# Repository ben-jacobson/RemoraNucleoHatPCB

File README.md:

# Remora Nucleo-144 Hat PCB.
Work in progress design for a cost-effective, highly customisable LinuxCNC motion control unit.

Form factor is a hat/shield for ST Nucleo-144 evaluation board running [Remora](https://github.com/scottalford75/Remora). Requires a WIZNet TOE for Ethernet control. A link to a specific recommended version of Remora can be found below but other versions should work. This unit is capable of controlling a variety of machine types including CNC milling machines, routers, lathes, laser and plasma cutters. 

Schematics and board layout are editable with Kicad 9. Gerbers and PDF's of the schematics will become available on release. At this stage the design is pre-release with a lot of validation/testing/design work pending. 

## Proposed Features
- **Low cost**: Board can be fabricated via PCBWay, parts can be ordered from Digikey/Mouser/Element14. Digikey part numbers are written into the BOM for easy ordering. My latest build was sponsored by PCBWay but their estimated cost was just under the $100USD mark not including shipping 
- **Approachable**: Goal is to be well documented, providing step by step build guides.
- **Moderate skill requirement**: SMT soldering skills are required but the pad sizes are forgiving enough for hand soldering. Hot air or reflow oven soldering is possible but not required. 

## Current spec
- Nucleo-144 Hat for 6 axis LinuxCNC motion control using custom port of Remora built for STM32. Board may also support GrblHAL but is not yet tested. 
- Up to 6 axes of isolated, step generation. Default max step gen rate in Remora is 40Khz but the driver circuitry has been tested to generate clean step pulses up to 100Khz. Can be used with any 5V single ended or differential stepper driver. Unused axes can be reconfigured as differential digital outputs. 
- IO: 16x digital inputs, 8x NPN digital outputs. Outputs are sink logic/open collector, protected by a fuse and can sink up to 40mA of current. 
- Most outputs can be configured to drive PWM signals, see the readme in the firmware below for available pins and how to configure this.
- IO: 2x analog inputs (non isolated)
- 1x 0-5v / 0-10v DAC for spindle control. Additional spindle control such as direction or indexing can be achieved with IO.
- 24V DC power input for powering the Nucleo which in turn supplies 5V and 3.3V to sections of the board that are isolated. Galvanic isolation between Nucleo and external devices is achieved by supplying your own isolated 24V supply to the separate input. A jumper can be configured on board to powering the board with only one supply, but will break the isolation.  
- Console logging is available via a UART header (TX only, RX is not used by firmware).

## Future Specs
- PSU's seem to be fine handling 18-28V, need to test this before officially marking this as in spec. 
- There is an experimental single ended ABZ Rotary Encoder Input, it was hobbled together from parts already available on the BOM as an experiment. Predictably it does not perform any high speed task, it would probably even struggle with a slowly moved rotary encoder pot. Will eventually replace with a real design. 

## Build guide
This is intended to be a DIY project, not as a complete product.
A link will soon be provided to a place to order on PCBWay, or you can self source the parts using the DigiKey part numbers.
Please see the jumper settings and connecting to USB section as they are contain important information needed to get started.

**Jumper settings:**
Before powering on your Nucleo hat, ensure that the following two jumpers are set: 
JP1: Please remove this jumper entirely
JP3: Place to the far right position, indicating VIN as per the picture in JP3Setting.png

**Connecting to USB:**
Take care when connecting the device to USB. Please make sure that the board is fully powered up before connecting to USB. Failing to do so could result in damage to your computer. This is not an issue with our design, but in the Nucleo itself. For more info see 7.4.2 in the Nucleo 144 datasheet. The device does not need USB to run. USB can be used to flash new firmware or monitor serial output. For serial output, the provided TX pin header is a better choice if you'd like constant serial monitoring during use.

## Todos
- Perform full board testing with a real load and measure current draws, re-design the PSU's for beter efficiency, line/load regulation, ripple rejection, etc. 
- Add PTC resettable fuses to PSU
- Commit release Gerber files to repo and PDF
- Put up some photos of the completed PCB.
- Put up marketplace product on PCBWay
- Research how we might be able to support Servo drives
- Test GRBLHal

## If you'd like to contribute into this project
Reach out - would love some help with any improvement. Would be especially grateful for anyone willing to help with testing, further engineering support, etc.

## Firmware
Firmware can be found in separate repo: https://github.com/ben-jacobson/Remora-STM32F4xx-PIO

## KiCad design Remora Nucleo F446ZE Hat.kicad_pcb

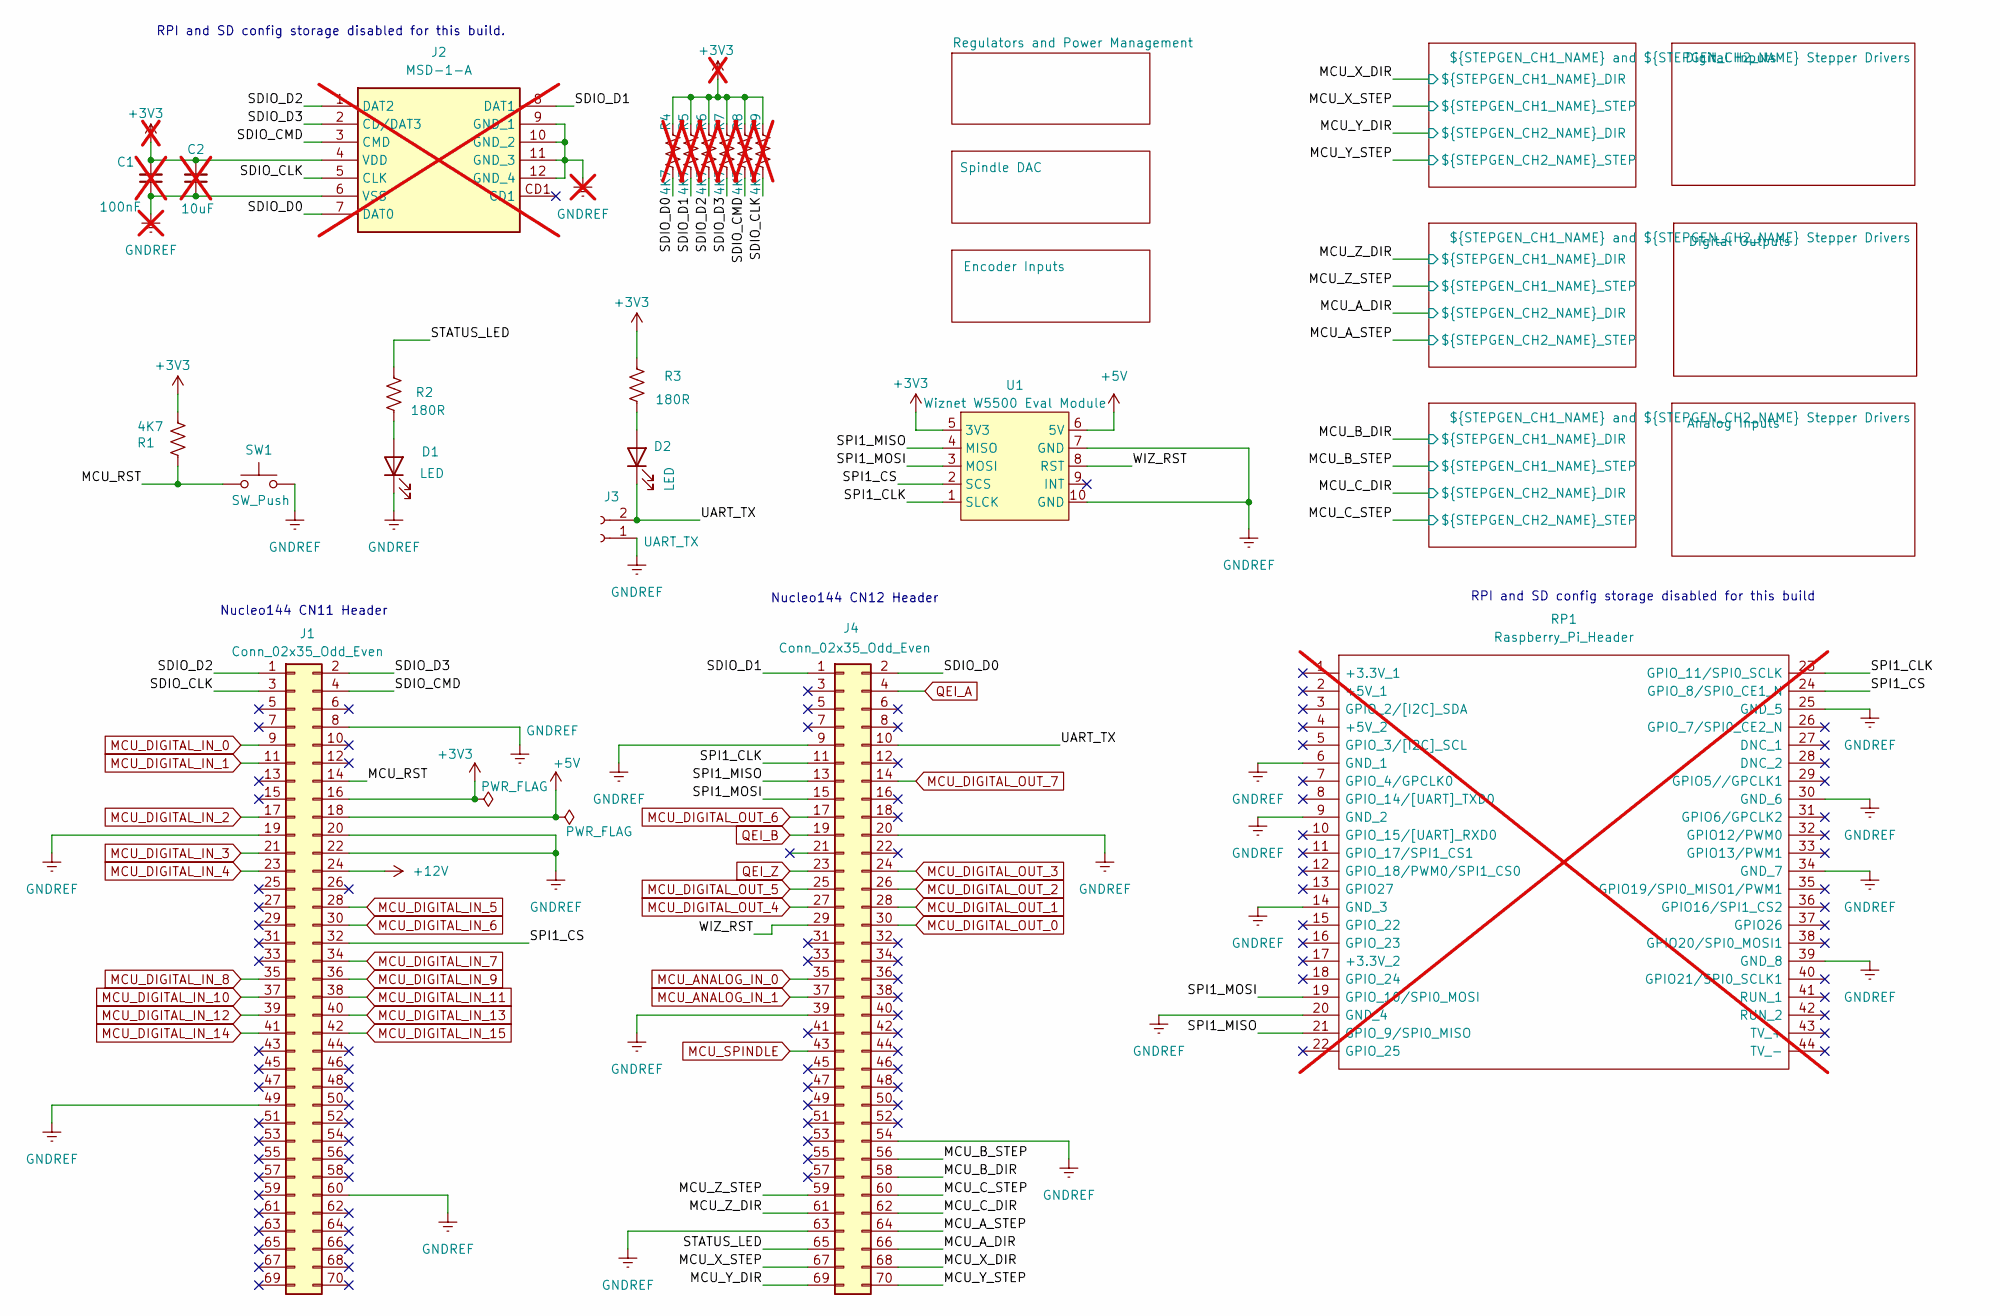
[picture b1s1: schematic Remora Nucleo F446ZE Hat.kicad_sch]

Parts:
C1: 100nF; C_1206_3216Metric_Pad1.33x1.80mm_HandSolder; Digikey Part Number 399-C1206C104K5RACTUCT-ND; not fitted
C2: 10uF; C_1206_3216Metric_Pad1.33x1.80mm_HandSolder; Digikey Part Number 1276-1804-1-ND; not fitted
D1, D2: LED; D_1206_3216Metric_Pad1.42x1.75mm_HandSolder; Digikey Part Number 3147-B1501USD-20D000313U1930CT-ND
J1, J4: Conn_02x35_Odd_Even; PinHeader_2x35_P2.54mm_Vertical; Digikey Part Number SSW-135-03-T-D-ND
J2: MSD-1-A; MSD1A; Manufacturer_Part_Number MSD-1-A; Mouser Part Number 179-MSD-1-A; not fitted
J3: UART_TX; PinHeader_1x02_P2.54mm_Vertical; Digikey Part Number PH1-02-UA
R1: 4K7; R_1206_3216Metric_Pad1.30x1.75mm_HandSolder; Digikey Part Number 311-4.70KFRCT-ND
R2, R3: 180R; R_1206_3216Metric_Pad1.30x1.75mm_HandSolder; Digikey Part Number 311-180FRCT-ND
R4, R5, R6, R7, R8, R9: 4K7; R_1206_3216Metric_Pad1.30x1.75mm_HandSolder; Digikey Part Number 311-4.70KFRCT-ND; not fitted
RP1: Raspberry_Pi_Header; raspberrypi_2_3; Manufacturer_Part_Number Raspberry Pi 2 or 3; Digikey Part Number SAM1204-20-ND; not fitted
SW1: SW_Push; SW_SPST_Omron_B3FS-100xP; Digikey Part Number SW424CT-ND
U1: Wiznet W5500 Eval Module; W5500EvalModule; Digikey Part Number SAM12520-ND

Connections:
+3V3: C1.2, C2.2, J1.16, J2.4 (VDD), R1.1, R3.1, R4.1, R5.1, R6.1, R7.1, R8.1, R9.1, U1.5 (3V3); also elsewhere on the board
+5V: J1.18, U1.6 (5V)
+12V: J1.24; also elsewhere on the board
/MCU_A_DIR: J4.66; also elsewhere on the board
/MCU_A_STEP: J4.64; also elsewhere on the board
/MCU_B_DIR: J4.58; also elsewhere on the board
/MCU_B_STEP: J4.56; also elsewhere on the board
/MCU_C_DIR: J4.62; also elsewhere on the board
/MCU_C_STEP: J4.60; also elsewhere on the board
/MCU_RST: J1.14, R1.2, SW1.1
/MCU_X_DIR: J4.68; also elsewhere on the board
/MCU_X_STEP: J4.67; also elsewhere on the board
/MCU_Y_DIR: J4.69; also elsewhere on the board
/MCU_Y_STEP: J4.70; also elsewhere on the board
/MCU_Z_DIR: J4.61; also elsewhere on the board
/MCU_Z_STEP: J4.59; also elsewhere on the board
/SDIO_CLK: J1.3, J2.5 (CLK), R9.2
/SDIO_CMD: J1.4, J2.3 (CMD), R8.2
/SDIO_D0: J2.7 (DAT0), J4.2, R4.2
/SDIO_D1: J2.8 (DAT1), J4.1, R5.2
/SDIO_D2: J1.1, J2.1 (DAT2), R6.2
/SDIO_D3: J1.2, J2.2 (CD/DAT3), R7.2
/SPI1_CLK: J4.11, RP1.23 (GPIO_11/SPI0_SCLK), U1.1 (SLCK)
/SPI1_CS: J1.32, RP1.24 (GPIO_8/SPI0_CE1_N), U1.2 (SCS)
/SPI1_MISO: J4.13, RP1.21 (GPIO_9/SPI0_MISO), U1.4 (MISO)
/SPI1_MOSI: J4.15, RP1.19 (GPIO_10/SPI0_MOSI), U1.3 (MOSI)
/STATUS_LED: J4.65, R2.1
/UART_TX: D2.1 (K), J3.2, J4.10
/WIZ_RST: J4.29, U1.8 (RST)
GNDREF: C1.1, C2.1, D1.1 (K), J1.8, J1.19, J1.20, J1.22, J1.49, J1.60, J2.6 (VSS), J2.9 (GND_1), J2.10 (GND_2), J2.11 (GND_3), J2.12 (GND_4), J3.1, J4.9, J4.20, J4.39, J4.54, J4.63, RP1.6 (GND_1), RP1.9 (GND_2), RP1.14 (GND_3), RP1.20 (GND_4), RP1.25 (GND_5), RP1.30 (GND_6), RP1.34 (GND_7), RP1.39 (GND_8), SW1.2, U1.7 (GND), U1.10 (GND); also elsewhere on the board
MCU_ANALOG_IN_0: J4.35; also elsewhere on the board
MCU_ANALOG_IN_1: J4.37; also elsewhere on the board
MCU_DIGITAL_IN_0: J1.9; also elsewhere on the board
MCU_DIGITAL_IN_1: J1.11; also elsewhere on the board
MCU_DIGITAL_IN_2: J1.17; also elsewhere on the board
MCU_DIGITAL_IN_3: J1.21; also elsewhere on the board
MCU_DIGITAL_IN_4: J1.23; also elsewhere on the board
MCU_DIGITAL_IN_5: J1.28; also elsewhere on the board
MCU_DIGITAL_IN_6: J1.30; also elsewhere on the board
MCU_DIGITAL_IN_7: J1.34; also elsewhere on the board
MCU_DIGITAL_IN_8: J1.35; also elsewhere on the board
MCU_DIGITAL_IN_9: J1.36; also elsewhere on the board
MCU_DIGITAL_IN_10: J1.37; also elsewhere on the board
MCU_DIGITAL_IN_11: J1.38; also elsewhere on the board
MCU_DIGITAL_IN_12: J1.39; also elsewhere on the board
MCU_DIGITAL_IN_13: J1.40; also elsewhere on the board
MCU_DIGITAL_IN_14: J1.41; also elsewhere on the board
MCU_DIGITAL_IN_15: J1.42; also elsewhere on the board
MCU_DIGITAL_OUT_0: J4.30; also elsewhere on the board
MCU_DIGITAL_OUT_1: J4.28; also elsewhere on the board
MCU_DIGITAL_OUT_2: J4.26; also elsewhere on the board
MCU_DIGITAL_OUT_3: J4.24; also elsewhere on the board
MCU_DIGITAL_OUT_4: J4.27; also elsewhere on the board
MCU_DIGITAL_OUT_5: J4.25; also elsewhere on the board
MCU_DIGITAL_OUT_6: J4.17; also elsewhere on the board
MCU_DIGITAL_OUT_7: J4.14; also elsewhere on the board
MCU_SPINDLE: J4.43; also elsewhere on the board
unnamed: D1.2 (A), R2.2
unnamed: D2.2 (A), R3.2
QEI_A: J4.4; also elsewhere on the board
QEI_B: J4.19; also elsewhere on the board
QEI_Z: J4.23; also elsewhere on the board

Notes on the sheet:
RPI and SD config storage disabled for this build.
RPI and SD config storage disabled for this build
Nucleo144 CN12 Header
Nucleo144 CN11 Header

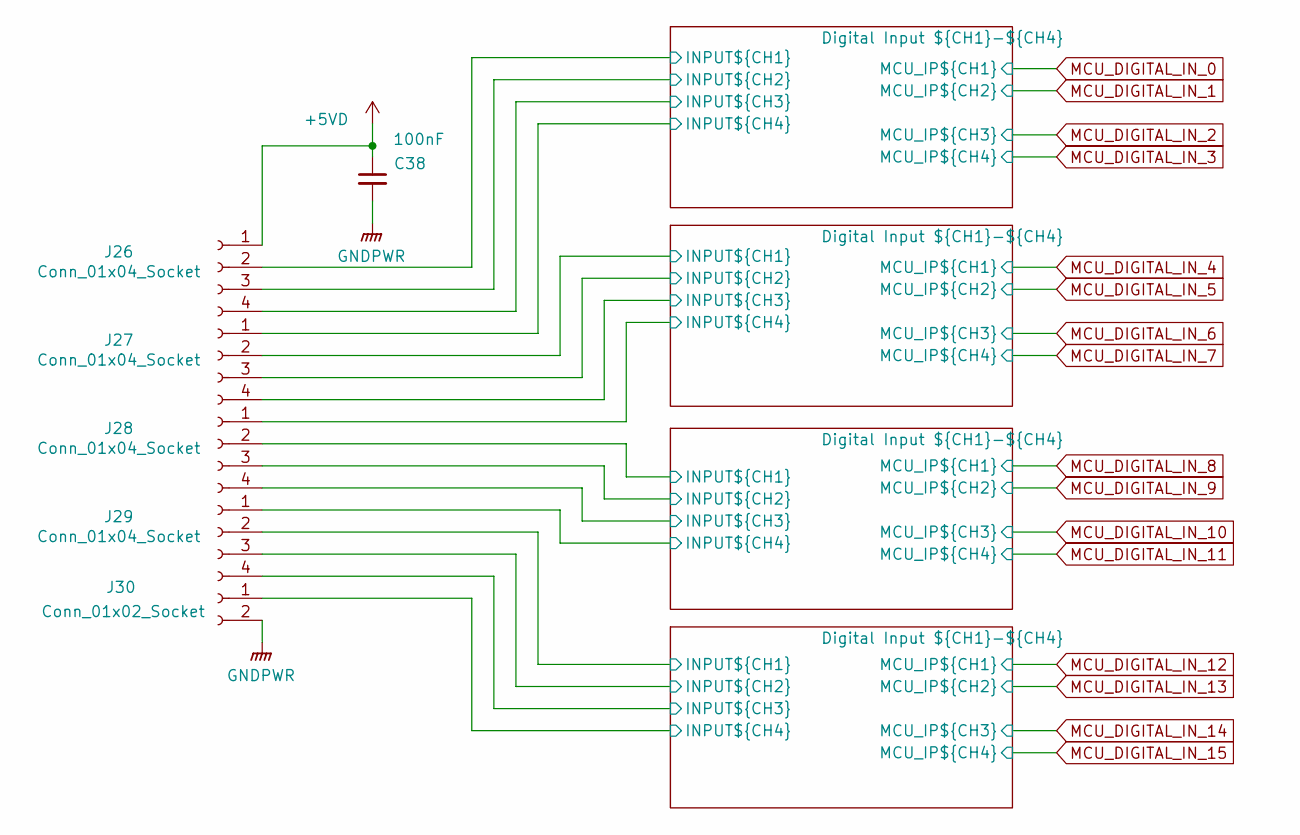
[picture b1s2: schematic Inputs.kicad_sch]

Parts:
C38: 100nF; C_1206_3216Metric_Pad1.33x1.80mm_HandSolder; Digikey Part Number 399-C1206C104K5RACTUCT-ND
J26, J27, J28, J29: Conn_01x04_Socket; 691412120004B; Digikey Part Number 732-691412120004B-ND
J30: Conn_01x02_Socket; 691412120002B; Digikey Part Number 732-691412120002B-ND

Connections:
+5VD: C38.1, J26.1; also elsewhere on the board
/Digital Inputs/Digital Input 0-3/INPUT0: J26.2; also elsewhere on the board
/Digital Inputs/Digital Input 0-3/INPUT1: J26.3; also elsewhere on the board
/Digital Inputs/Digital Input 0-3/INPUT2: J26.4; also elsewhere on the board
/Digital Inputs/Digital Input 0-3/INPUT3: J27.1; also elsewhere on the board
/Digital Inputs/Digital Input 4-7/INPUT4: J27.2; also elsewhere on the board
/Digital Inputs/Digital Input 4-7/INPUT5: J27.3; also elsewhere on the board
/Digital Inputs/Digital Input 4-7/INPUT6: J27.4; also elsewhere on the board
/Digital Inputs/Digital Input 4-7/INPUT7: J28.1; also elsewhere on the board
/Digital Inputs/Digital Input 8-11/INPUT8: J28.2; also elsewhere on the board
/Digital Inputs/Digital Input 8-11/INPUT9: J28.3; also elsewhere on the board
/Digital Inputs/Digital Input 8-11/INPUT10: J28.4; also elsewhere on the board
/Digital Inputs/Digital Input 8-11/INPUT11: J29.1; also elsewhere on the board
/Digital Inputs/Digital Input 12-15/INPUT12: J29.2; also elsewhere on the board
/Digital Inputs/Digital Input 12-15/INPUT13: J29.3; also elsewhere on the board
/Digital Inputs/Digital Input 12-15/INPUT14: J29.4; also elsewhere on the board
/Digital Inputs/Digital Input 12-15/INPUT15: J30.1; also elsewhere on the board
GNDPWR: C38.2, J30.2; also elsewhere on the board

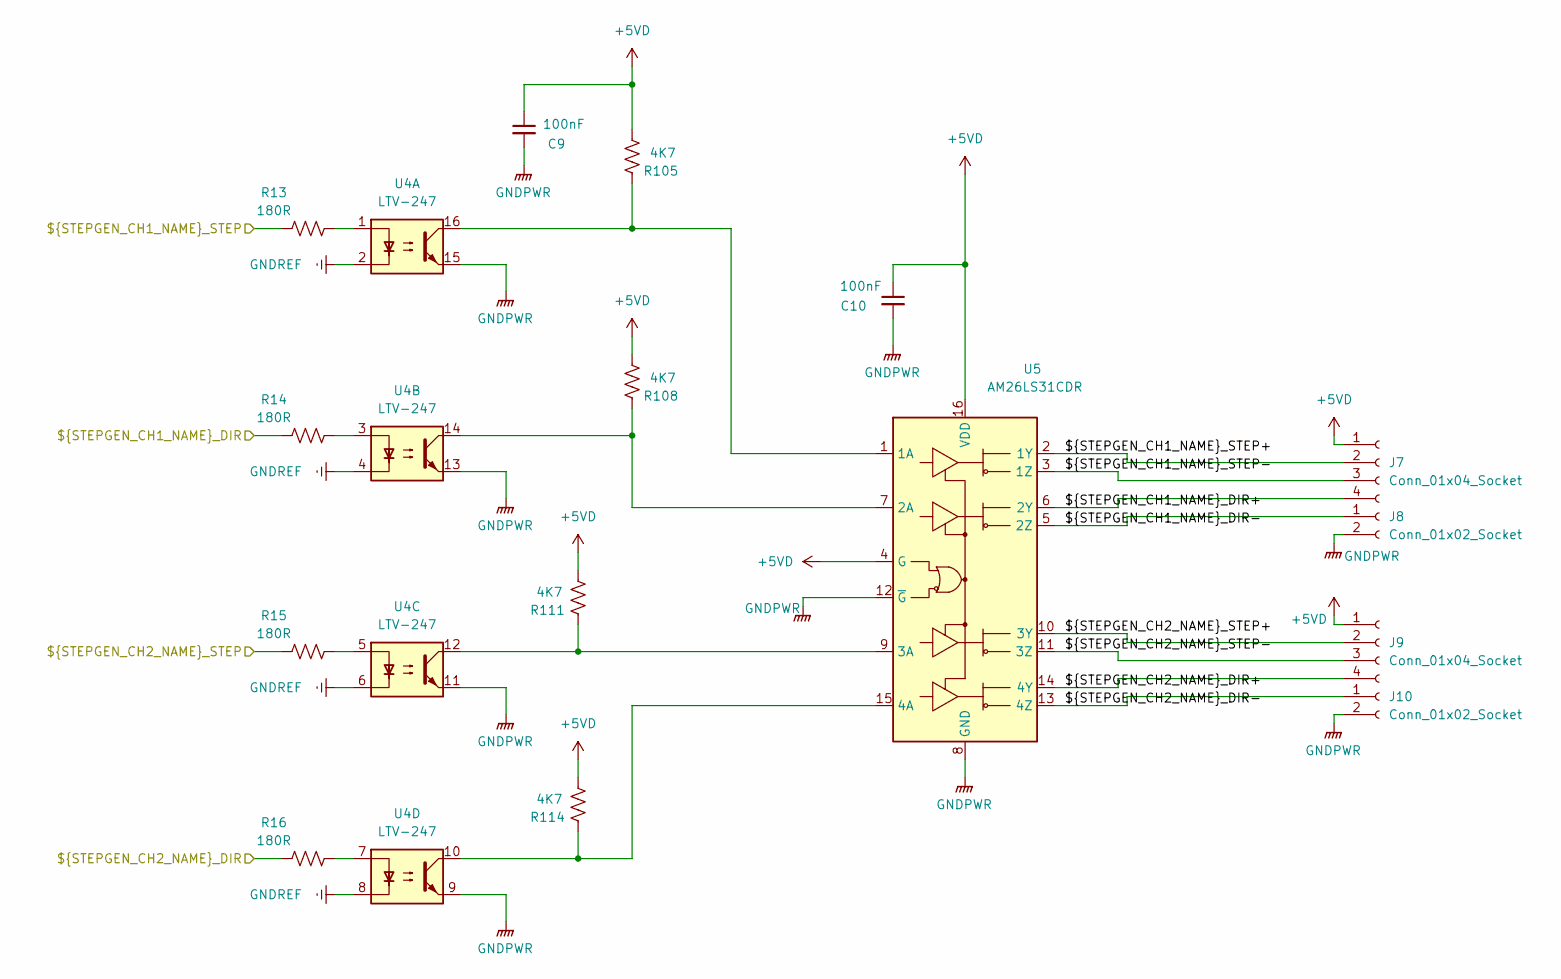
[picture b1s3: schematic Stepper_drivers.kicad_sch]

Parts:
C9, C10: 100nF; C_1206_3216Metric_Pad1.33x1.80mm_HandSolder; Digikey Part Number 399-C1206C104K5RACTUCT-ND
J7, J9: Conn_01x04_Socket; 691412120004B; Digikey Part Number 732-691412120004B-ND
J8, J10: Conn_01x02_Socket; 691412120002B; Digikey Part Number 732-691412120002B-ND
R13, R14, R15, R16: 180R; R_1206_3216Metric_Pad1.30x1.75mm_HandSolder; Digikey Part Number 311-180FRCT-ND
R105, R108, R111, R114: 4K7; R_1206_3216Metric_Pad1.30x1.75mm_HandSolder; Digikey Part Number 311-4.70KFRCT-ND
U4: LTV-247; SOP-16_4.4x10.4mm_P1.27mm; Digikey Part Number 160-2255-1-ND
U5: AM26LS31CDR; SOIC-16_3.9x9.9mm_P1.27mm; JLCPCB Part #（optional） C3019542

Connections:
+5VD: C9.1, C10.1, J7.1, J9.1, R105.2, R108.2, R111.2, R114.2, U5.4 (G), U5.16 (VDD); also elsewhere on the board
/MCU_X_DIR: R14.1; also elsewhere on the board
/MCU_X_STEP: R13.1; also elsewhere on the board
/MCU_Y_DIR: R16.1; also elsewhere on the board
/MCU_Y_STEP: R15.1; also elsewhere on the board
/X and Y Stepper Drivers/X_DIR+: J7.4, U5.6 (2Y)
/X and Y Stepper Drivers/X_DIR-: J8.1, U5.5 (2Z)
/X and Y Stepper Drivers/X_STEP+: J7.2, U5.2 (1Y)
/X and Y Stepper Drivers/X_STEP-: J7.3, U5.3 (1Z)
/X and Y Stepper Drivers/Y_DIR+: J9.4, U5.14 (4Y)
/X and Y Stepper Drivers/Y_DIR-: J10.1, U5.13 (4Z)
/X and Y Stepper Drivers/Y_STEP+: J9.2, U5.10 (3Y)
/X and Y Stepper Drivers/Y_STEP-: J9.3, U5.11 (3Z)
GNDPWR: C9.2, C10.2, J8.2, J10.2, U4.9, U4.11, U4.13, U4.15, U5.8 (GND), U5.12 (~G); also elsewhere on the board
GNDREF: U4.2, U4.4, U4.6, U4.8; also elsewhere on the board
unnamed: R13.2, U4.1
unnamed: R14.2, U4.3
unnamed: R15.2, U4.5
unnamed: R16.2, U4.7
unnamed: R105.1, U4.16, U5.1 (1A)
unnamed: R108.1, U4.14, U5.7 (2A)
unnamed: R111.1, U4.12, U5.9 (3A)
unnamed: R114.1, U4.10, U5.15 (4A)

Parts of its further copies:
C15, C16, C21, C22: 100nF; C_1206_3216Metric_Pad1.33x1.80mm_HandSolder; Digikey Part Number 399-C1206C104K5RACTUCT-ND
J11, J13, J15, J17: Conn_01x04_Socket; 691412120004B; Digikey Part Number 732-691412120004B-ND
J12, J14, J16, J18: Conn_01x02_Socket; 691412120002B; Digikey Part Number 732-691412120002B-ND
R53, R54, R55, R56, R69, R70, R71, R72: 180R; R_1206_3216Metric_Pad1.30x1.75mm_HandSolder; Digikey Part Number 311-180FRCT-ND
R106, R107, R109, R110, R112, R113, R115, R116: 4K7; R_1206_3216Metric_Pad1.30x1.75mm_HandSolder; Digikey Part Number 311-4.70KFRCT-ND
U12, U14: LTV-247; SOP-16_4.4x10.4mm_P1.27mm; Digikey Part Number 160-2255-1-ND
U13, U15: AM26LS31CDR; SOIC-16_3.9x9.9mm_P1.27mm; JLCPCB Part #（optional） C3019542

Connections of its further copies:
+5VD: C15.1, C16.1, C21.1, C22.1, J11.1, J13.1, J15.1, J17.1, R106.2, R107.2, R109.2, R110.2, R112.2, R113.2, R115.2, R116.2, U13.4 (G), U13.16 (VDD), U15.4 (G), U15.16 (VDD); also elsewhere on the board
/B and C Stepper Drivers/B_DIR+: J15.4, U15.6 (2Y)
/B and C Stepper Drivers/B_DIR-: J16.1, U15.5 (2Z)
/B and C Stepper Drivers/B_STEP+: J15.2, U15.2 (1Y)
/B and C Stepper Drivers/B_STEP-: J15.3, U15.3 (1Z)
/B and C Stepper Drivers/C_DIR+: J17.4, U15.14 (4Y)
/B and C Stepper Drivers/C_DIR-: J18.1, U15.13 (4Z)
/B and C Stepper Drivers/C_STEP+: J17.2, U15.10 (3Y)
/B and C Stepper Drivers/C_STEP-: J17.3, U15.11 (3Z)
/MCU_A_DIR: R56.1; also elsewhere on the board
/MCU_A_STEP: R55.1; also elsewhere on the board
/MCU_B_DIR: R70.1; also elsewhere on the board
/MCU_B_STEP: R69.1; also elsewhere on the board
/MCU_C_DIR: R72.1; also elsewhere on the board
/MCU_C_STEP: R71.1; also elsewhere on the board
/MCU_Z_DIR: R54.1; also elsewhere on the board
/MCU_Z_STEP: R53.1; also elsewhere on the board
/Z and A Stepper Drivers/A_DIR+: J13.4, U13.14 (4Y)
/Z and A Stepper Drivers/A_DIR-: J14.1, U13.13 (4Z)
/Z and A Stepper Drivers/A_STEP+: J13.2, U13.10 (3Y)
/Z and A Stepper Drivers/A_STEP-: J13.3, U13.11 (3Z)
/Z and A Stepper Drivers/Z_DIR+: J11.4, U13.6 (2Y)
/Z and A Stepper Drivers/Z_DIR-: J12.1, U13.5 (2Z)
/Z and A Stepper Drivers/Z_STEP+: J11.2, U13.2 (1Y)
/Z and A Stepper Drivers/Z_STEP-: J11.3, U13.3 (1Z)
GNDPWR: C15.2, C16.2, C21.2, C22.2, J12.2, J14.2, J16.2, J18.2, U12.9, U12.11, U12.13, U12.15, U13.8 (GND), U13.12 (~G), U14.9, U14.11, U14.13, U14.15, U15.8 (GND), U15.12 (~G); also elsewhere on the board
GNDREF: U12.2, U12.4, U12.6, U12.8, U14.2, U14.4, U14.6, U14.8; also elsewhere on the board
unnamed: R53.2, U12.1
unnamed: R54.2, U12.3
unnamed: R55.2, U12.5
unnamed: R56.2, U12.7
unnamed: R69.2, U14.1
unnamed: R70.2, U14.3
unnamed: R71.2, U14.5
unnamed: R72.2, U14.7
unnamed: R106.1, U12.16, U13.1 (1A)
unnamed: R109.1, U12.14, U13.7 (2A)
unnamed: R112.1, U12.12, U13.9 (3A)
unnamed: R115.1, U12.10, U13.15 (4A)
unnamed: R107.1, U14.16, U15.1 (1A)
unnamed: R110.1, U14.14, U15.7 (2A)
unnamed: R113.1, U14.12, U15.9 (3A)
unnamed: R116.1, U14.10, U15.15 (4A)

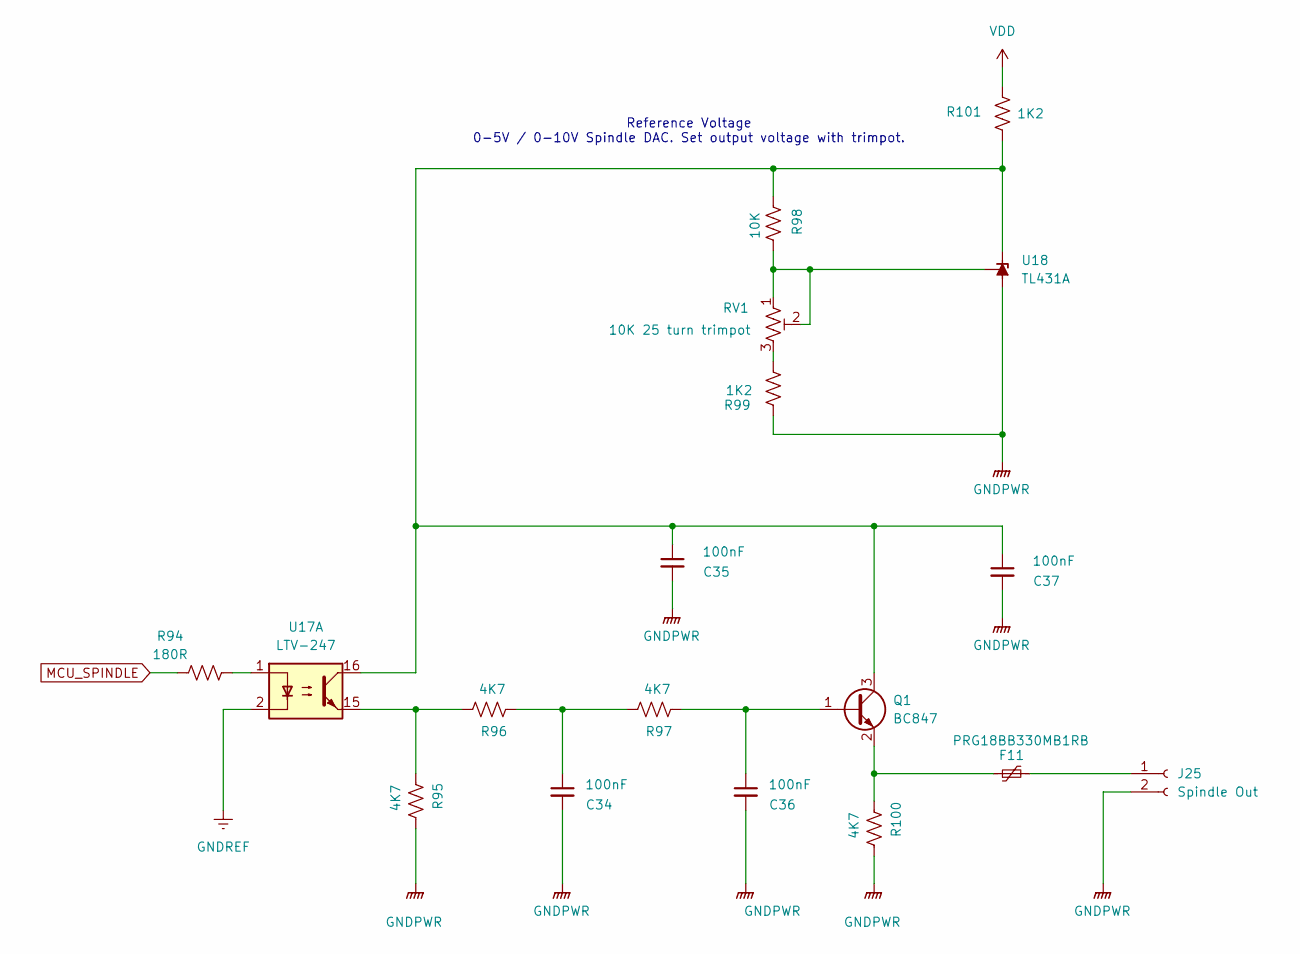
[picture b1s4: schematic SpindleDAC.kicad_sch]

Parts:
C34, C35, C36, C37: 100nF; C_1206_3216Metric_Pad1.33x1.80mm_HandSolder; Digikey Part Number 399-C1206C104K5RACTUCT-ND
F11: PRG18BB330MB1RB; Fuse_0603_1608Metric_Pad1.05x0.95mm_HandSolder; Digikey Part Number 490-2471-1-ND
J25: Spindle Out; 691412120002B; Digikey Part Number 732-691412120002B-ND
Q1: BC847; SOT-23; Digikey Part Number BC847CLT1GOSCT-ND
R94: 180R; R_1206_3216Metric_Pad1.30x1.75mm_HandSolder; Digikey Part Number 311-180FRCT-ND
R95, R96, R97, R100: 4K7; R_1206_3216Metric_Pad1.30x1.75mm_HandSolder; Digikey Part Number 311-4.70KFRCT-ND
R98: 10K; R_1206_3216Metric_Pad1.30x1.75mm_HandSolder; Digikey Part Number 311-10.0KFRCT-ND
R99, R101: 1K2; R_1206_3216Metric_Pad1.30x1.75mm_HandSolder; Digikey Part Number RMCF1206JT1K20CT-ND
RV1: 10K 25 turn trimpot; Potentiometer_Bourns_3266Y_Vertical; Digikey Part Number 118-PV36W103C01B00-ND
U17: LTV-247; SOP-16_4.4x10.4mm_P1.27mm; Digikey Part Number 160-2255-1-ND
U18: TL431A; SOT-23; Digikey Part Number 4878-MMTL431ACT-ND

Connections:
GNDPWR: C34.2, C35.2, C36.2, C37.2, J25.2, R95.2, R99.1, R100.2, U18.3 (A); also elsewhere on the board
GNDREF: U17.2; also elsewhere on the board
MCU_SPINDLE: R94.1; also elsewhere on the board
unnamed: C34.1, R96.1, R97.2
unnamed: F11.2, J25.1
unnamed: C36.1, Q1.1 (B), R97.1
unnamed: C35.1, C37.1, Q1.3 (C), R98.1, R101.1, U17.16, U18.2 (K)
unnamed: F11.1, Q1.2 (E), R100.1
unnamed: R94.2, U17.1
unnamed: R95.1, R96.2, U17.15
unnamed: R99.2, RV1.3
unnamed: R98.2, RV1.1, RV1.2, U18.1 (REF)
VDD: R101.2; also elsewhere on the board

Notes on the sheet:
Reference Voltage 0-5V / 0-10V Spindle DAC. Set output voltage with trimpot.

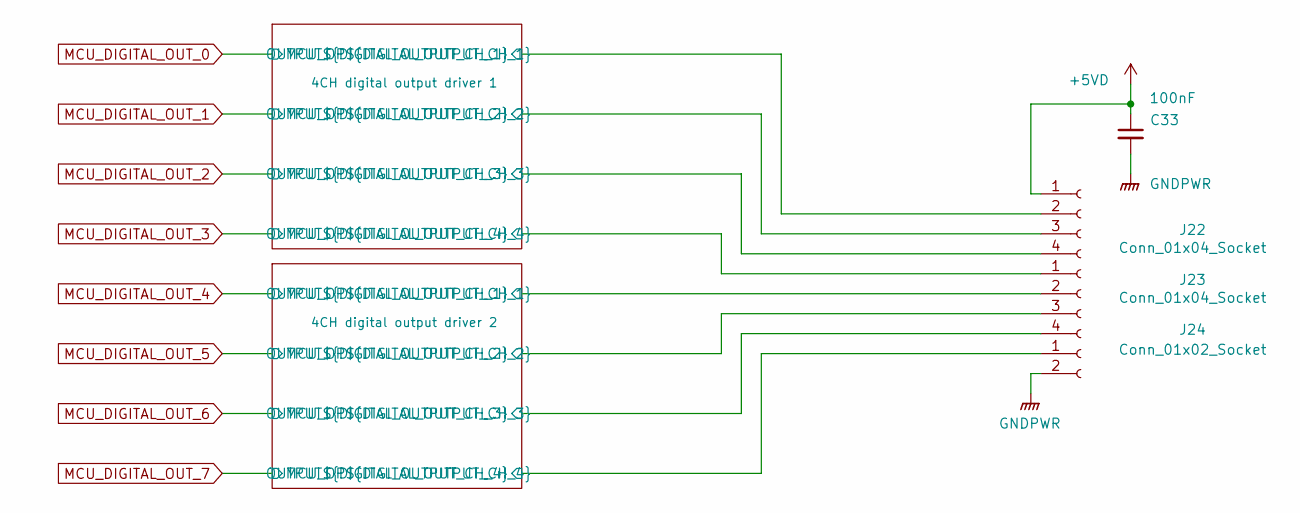
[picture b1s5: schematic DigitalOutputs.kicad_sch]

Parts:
C33: 100nF; C_1206_3216Metric_Pad1.33x1.80mm_HandSolder; Digikey Part Number 399-C1206C104K5RACTUCT-ND
J22, J23: Conn_01x04_Socket; 691412120004B; Digikey Part Number 732-691412120004B-ND
J24: Conn_01x02_Socket; 691412120002B; Digikey Part Number 732-691412120002B-ND

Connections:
+5VD: C33.1, J22.1; also elsewhere on the board
/Digital Outputs/4CH digital output driver 1/OUTPUT0: J22.2; also elsewhere on the board
/Digital Outputs/4CH digital output driver 1/OUTPUT1: J22.3; also elsewhere on the board
/Digital Outputs/4CH digital output driver 1/OUTPUT2: J22.4; also elsewhere on the board
/Digital Outputs/4CH digital output driver 1/OUTPUT3: J23.1; also elsewhere on the board
/Digital Outputs/4CH digital output driver 2/OUTPUT4: J23.2; also elsewhere on the board
/Digital Outputs/4CH digital output driver 2/OUTPUT5: J23.3; also elsewhere on the board
/Digital Outputs/4CH digital output driver 2/OUTPUT6: J23.4; also elsewhere on the board
/Digital Outputs/4CH digital output driver 2/OUTPUT7: J24.1; also elsewhere on the board
GNDPWR: C33.2, J24.2; also elsewhere on the board

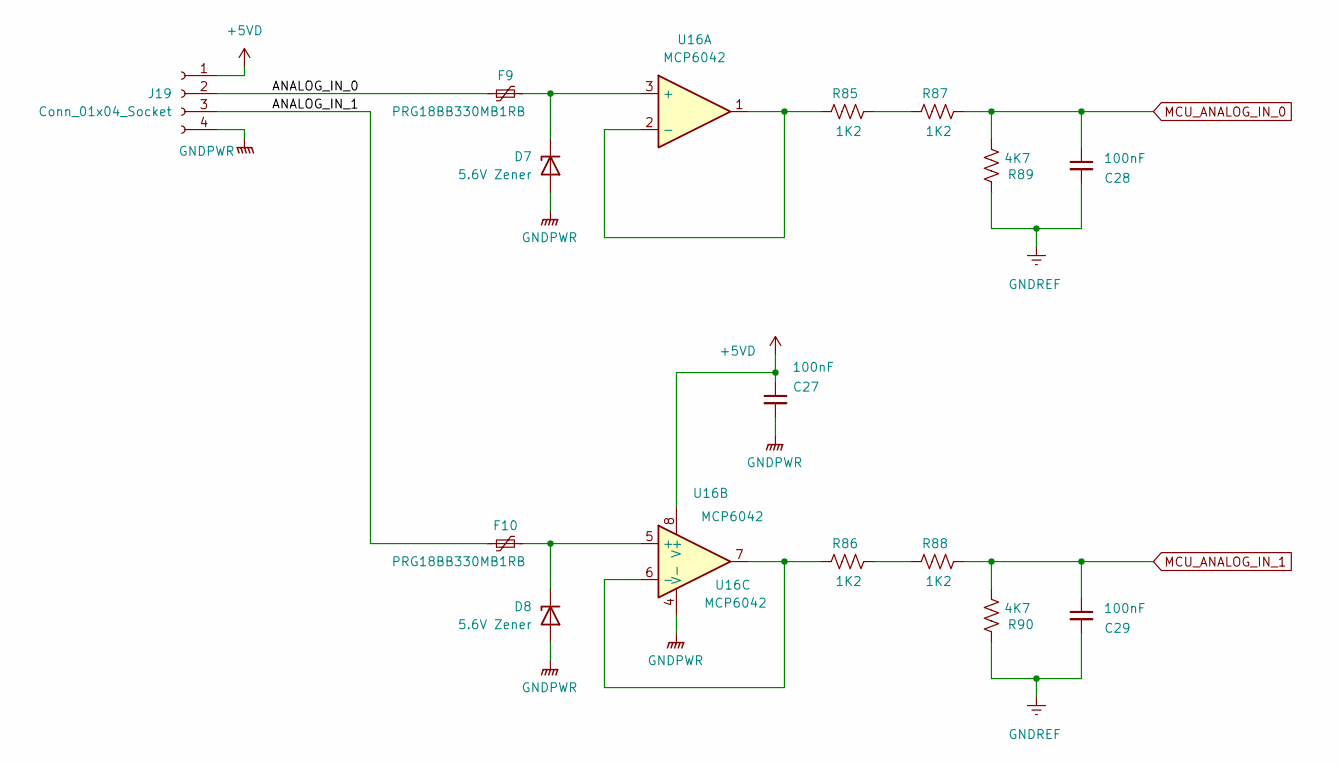
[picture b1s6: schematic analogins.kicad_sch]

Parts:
C27, C28, C29: 100nF; C_1206_3216Metric_Pad1.33x1.80mm_HandSolder; Digikey Part Number 399-C1206C104K5RACTUCT-ND
D7, D8: 5.6V Zener; SOT-23; Digikey Part Number SZMMBZ5232BLT1GOSCT-ND
F9, F10: PRG18BB330MB1RB; Fuse_0603_1608Metric_Pad1.05x0.95mm_HandSolder; Digikey Part Number 490-2471-1-ND
J19: Conn_01x04_Socket; 691412120004B; Digikey Part Number 732-691412120004B-ND
R85, R86, R87, R88: 1K2; R_1206_3216Metric_Pad1.30x1.75mm_HandSolder; Digikey Part Number RMCF1206JT1K20CT-ND
R89, R90: 4K7; R_1206_3216Metric_Pad1.30x1.75mm_HandSolder; Digikey Part Number 311-4.70KFRCT-ND
U16: MCP6042; SOIC-8_3.9x4.9mm_P1.27mm; Digikey Part Number MCP6042-I/SN-ND

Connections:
+5VD: C27.1, J19.1, U16.8 (V+); also elsewhere on the board
/Analog Inputs/ANALOG_IN_0: F9.1, J19.2
/Analog Inputs/ANALOG_IN_1: F10.1, J19.3
GNDPWR: C27.2, D7.1 (A), D8.1 (A), J19.4, U16.4 (V-); also elsewhere on the board
GNDREF: C28.2, C29.2, R89.1, R90.1; also elsewhere on the board
MCU_ANALOG_IN_0: C28.1, R87.1, R89.2; also elsewhere on the board
MCU_ANALOG_IN_1: C29.1, R88.1, R90.2; also elsewhere on the board
unnamed: D7.3 (K), F9.2, U16.3 (+)
unnamed: D8.3 (K), F10.2, U16.5 (+)
unnamed: R85.1, R87.2
unnamed: R86.1, R88.2
unnamed: R85.2, U16.1, U16.2 (-)
unnamed: R86.2, U16.6 (-), U16.7

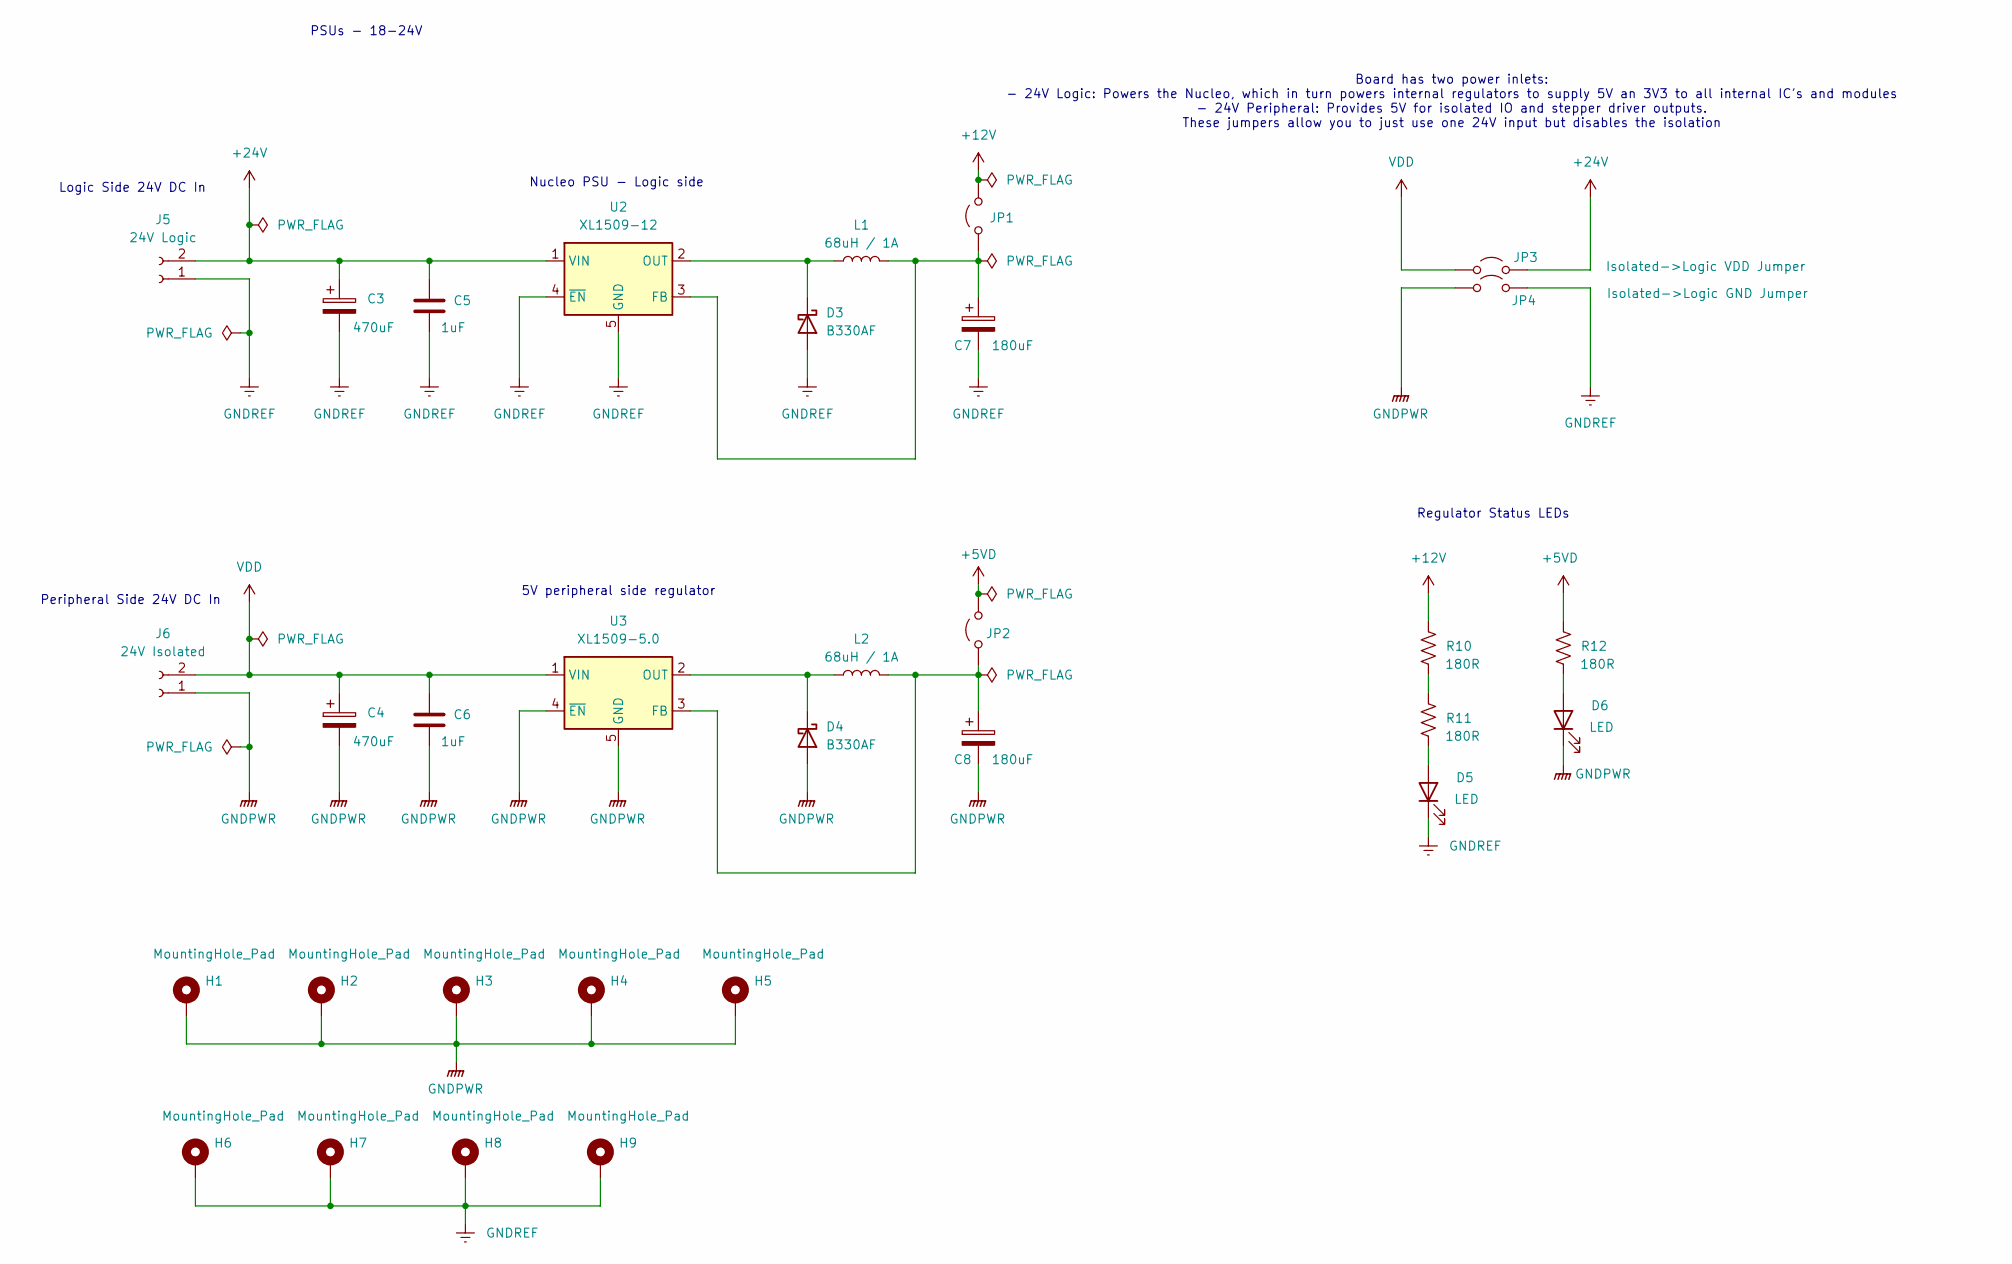
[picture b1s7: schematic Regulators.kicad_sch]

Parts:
C3, C4: 470uF; CP_Radial_D10.0mm_P5.00mm; Digikey Part Number 399-ESK477M050AH4KACT-ND
C5, C6: 1uF; C_1206_3216Metric_Pad1.33x1.80mm_HandSolder; Digikey Part Number 1276-1068-1-ND
C7, C8: 180uF; CP_Radial_D6.3mm_P2.50mm; Digikey Part Number 732-8633-1-ND
D3, D4: B330AF; D_SMA; Digikey Part Number B330AF-13DICT-ND
D5, D6: LED; D_1206_3216Metric_Pad1.42x1.75mm_HandSolder; Digikey Part Number 3147-B1501USD-20D000313U1930CT-ND
H1, H2, H3, H4, H5, H6, H7, H8, H9: MountingHole_Pad; MountingHole_2.7mm_M2.5_DIN965_Pad_TopBottom
J5: 24V Logic; 691412120002B; Digikey Part Number 732-691412120002B-ND
J6: 24V Isolated; 691412120002B; Digikey Part Number 732-691412120002B-ND
JP1, JP2: Peripheral->Logic VDD Jumper; SolderJumper-2_P1.3mm_Bridged2Bar_RoundedPad1.0x1.5mm; Digikey Part Number N/A
JP3: Isolated->Logic VDD Jumper; SolderJumper-2_P1.3mm_Open_RoundedPad1.0x1.5mm; Digikey Part Number N/A
JP4: Isolated->Logic GND Jumper; SolderJumper-2_P1.3mm_Open_RoundedPad1.0x1.5mm; Digikey Part Number N/A
L1, L2: 68uH / 1A; L_APV_ANR8040; Digikey Part Number SDE0805A-680KCT-ND
R10, R11, R12: 180R; R_1206_3216Metric_Pad1.30x1.75mm_HandSolder; Digikey Part Number 311-180FRCT-ND
U2: XL1509-12; SOIC-8_3.9x4.9mm_P1.27mm; Digikey Part Number 4518-XL1509-12CT-ND
U3: XL1509-5.0; SOIC-8_3.9x4.9mm_P1.27mm; Digikey Part Number 4518-XL1509-5.0CT-ND

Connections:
+5VD: JP2.2 (B), R12.1; also elsewhere on the board
+12V: JP1.2 (B), R10.1; also elsewhere on the board
+24V: C3.1, C5.1, J5.2, JP3.2 (B), U2.1 (VIN)
GNDPWR: C4.2, C6.2, C8.2, D4.2 (A), D6.1 (K), H1.1, H2.1, H3.1, H4.1, H5.1, J6.1, JP4.1 (A), U3.4 (~EN), U3.5 (GND), U3.6 (GND), U3.7 (GND), U3.8 (GND); also elsewhere on the board
GNDREF: C3.2, C5.2, C7.2, D3.2 (A), D5.1 (K), H6.1, H7.1, H8.1, H9.1, J5.1, JP4.2 (B), U2.4 (~EN), U2.5 (GND), U2.6 (GND), U2.7 (GND), U2.8 (GND); also elsewhere on the board
unnamed: D3.1 (K), L1.1, U2.2 (OUT)
unnamed: D4.1 (K), L2.1, U3.2 (OUT)
unnamed: D5.2 (A), R11.2
unnamed: D6.2 (A), R12.2
unnamed: C7.1, JP1.1 (A), L1.2, U2.3 (FB)
unnamed: C8.1, JP2.1 (A), L2.2, U3.3 (FB)
unnamed: R10.2, R11.1
VDD: C4.1, C6.1, J6.2, JP3.1 (A), U3.1 (VIN); also elsewhere on the board

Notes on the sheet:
Board has two power inlets: - 24V Logic: Powers the Nucleo, which in turn powers internal regulators to supply 5V an 3V3 to all internal IC's and modules - 24V Peripheral: Provides 5V for isolated IO and stepper driver outputs. These jumpers allow you to just use one 24V input but disables the isol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
5V peripheral side regulator
Nucleo PSU - Logic side
Logic Side 24V DC In
PSUs - 18-24V
Peripheral Side 24V DC In
Regulator Status LEDs

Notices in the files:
Remora Nucleo F446ZE Hat.kicad_pcb:
© 2026 Ben Jacobson
